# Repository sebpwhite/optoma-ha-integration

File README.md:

# Optoma Projector

Home Assistant custom integration for controlling an Optoma projector over
RS-232. It is designed to work with local serial ports and ESPHome serial
proxies through Home Assistant's serial port selector.

## Repository Layout

- `custom_components/optoma_projector/` contains the HACS-installable Home
  Assistant integration.
- `esphome/ProjectorController.yaml` contains the ESPHome firmware that exposes
  the projector UART as an ESPHome serial proxy.

## Basic Use

1. Flash the ESPHome firmware from `esphome/ProjectorController.yaml`.
2. Install the `optoma_projector` integration in Home Assistant.
3. Add the integration from the Home Assistant UI and select the ESPHome serial
   proxy from the serial port dropdown.

The current integration implements power, input selection, useful projector
settings, status sensors, and a re-sync action for the GT1080HDR.
Power state is polled regularly so Home Assistant notices manual power-button
changes and automatic shutdowns.

For detailed integration logs, enable debug logging for
`custom_components.optoma_projector`.

## Entities

- Media player: power and input source selection.
- Sensors: projector status, lamp hours, and temperature.
- Switches: AV mute, freeze, 3D mode, and 3D sync invert.
- Selects: display mode, aspect ratio, brightness mode, and 3D format.
- Numbers: brightness, contrast, and vertical keystone.
- Button: re-sync.

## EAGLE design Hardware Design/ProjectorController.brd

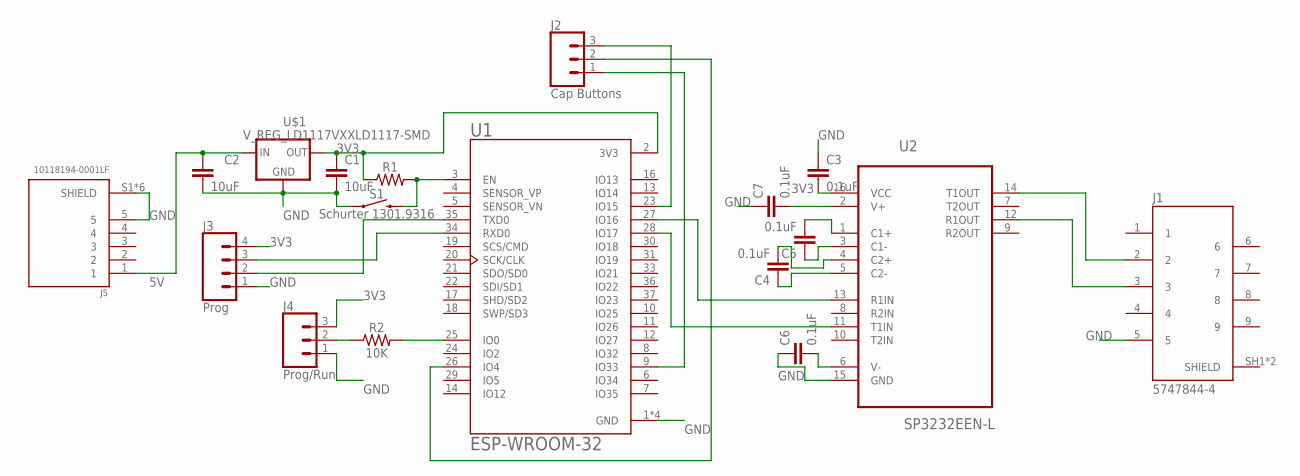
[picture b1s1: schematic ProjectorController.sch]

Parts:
C1, C2: 10uF; 1206
C3, C4, C5, C6, C7: 0.1uF; 1206
J1: 5747844-4; TE_5747844-4
J2: Cap Buttons; SCREWTERMINAL-3.5MM-3-NS
J3: Prog; 1X04
J4: Prog/Run; 1X03
J5: 10118194-0001LF; AMPHENOL_10118194-0001LF
R1: 1206
R2: 10K; 1206
S1: Schurter 1301.9316; TACTILE_SWITCH_SMD_6.2MM_TALL
U1: ESP-WROOM-32; MODULE_ESP-WROOM-32
U2: SP3232EEN-L; SOIC127P600X175-16N
U$1: V_REG_LD1117VXXLD1117-SMD; SOT223

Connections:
3V3: C1.1, C3.2, J3.4, J4.3, R1.1, U1.2 (3V3), U2.16 (VCC), U$1.2 (OUT)
5V: C2.1, J5.1, U$1.3 (IN)
GND: C1.2, C2.2, C3.1, C6.1, C7.1, J1.5, J3.1, J4.1, J5.5, J5.S1 (SHIELD), J5.S2 (SHIELD), J5.S3 (SHIELD), J5.S4 (SHIELD), J5.S5 (SHIELD), J5.S6 (SHIELD), S1.A2 (1), U1.1 (GND), U1.1.1 (GND), U1.15 (GND), U1.38 (GND), U2.15 (GND), U$1.1 (GND)
unnamed: J2.3, U1.23 (IO15)
unnamed: J2.1, U1.9 (IO33)
unnamed: J2.2, U1.26 (IO4)
unnamed: R1.2, S1.B2 (2), U1.3 (EN)
unnamed: R2.2, U1.25 (IO0)
unnamed: J4.2, R2.1
unnamed: J3.2, U1.35 (TXD0)
unnamed: J3.3, U1.34 (RXD0)
unnamed: U1.28 (IO17), U2.11 (T1IN)
unnamed: J1.2, U2.14 (T1OUT)
unnamed: J1.3, U2.12 (R1OUT)
unnamed: C5.2, U2.1 (C1+)
unnamed: U1.27 (IO16), U2.13 (R1IN)
unnamed: C5.1, U2.3 (C1-)
unnamed: C4.2, U2.4 (C2+)
unnamed: C4.1, U2.5 (C2-)
unnamed: C7.2, U2.2 (V+)
unnamed: C6.2, U2.6 (V-)

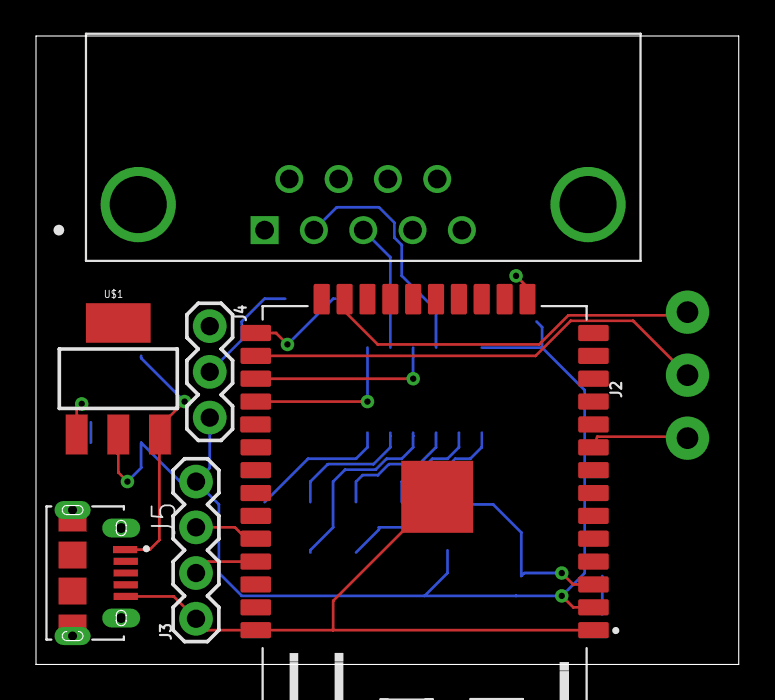
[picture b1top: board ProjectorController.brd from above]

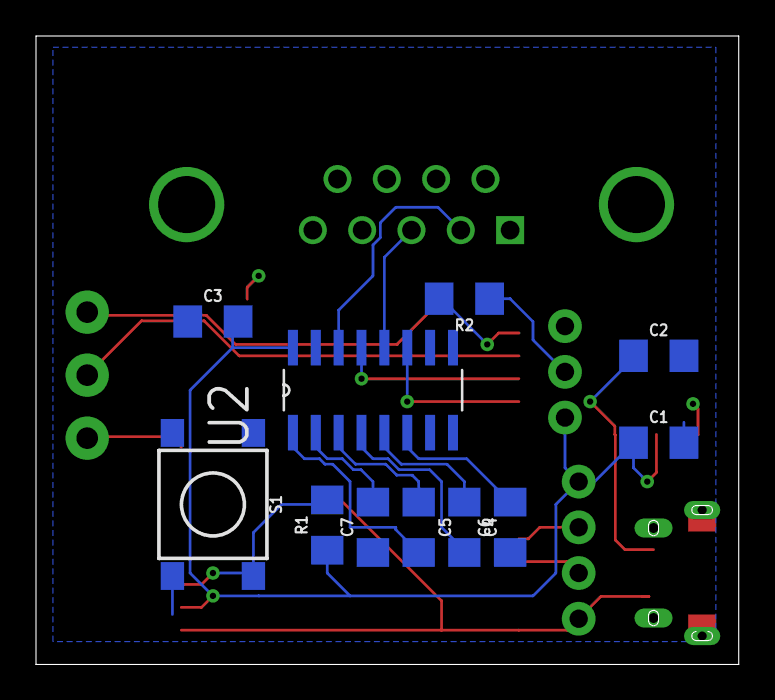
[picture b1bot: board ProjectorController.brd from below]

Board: 2 copper layers, 39.0 x 34.9 mm, 18 parts (11 on the bottom side), 21 nets.

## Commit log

2020-01-25 First cut of firmware with simple on/off commands working. PC-6
2020-01-25 Added touch sensor stuff and tied to to switches
2020-01-25 Revert "Added touch sensor stuff and tied to to switches"
    This reverts commit 2cf4c3fe7aaaa9ff7bf1352f440d9ed528192ab9.
2020-01-25 Revert "Revert "Added touch sensor stuff and tied to to switches""
    This reverts commit 99066c4c33003fed9244670f1164241629220ea0.
2020-01-25 First crack at custom component polling power state PC-10
2020-01-27 Custom Component Running Well
2020-01-28 Schematic started. PC-11
2020-01-29 USB port added and rough cut of schematic done. PC-11
2020-01-30 Progress on board layout PC-13
2020-01-31 Switched UART Pins PC-12
2020-02-01 Board Layout Complete PC-13
2020-02-02 Optimised Layout
2020-05-02 ED-33 Major board redesign to make smaller
2020-05-02 Revert "ED-33 Major board redesign to make smaller"
    This reverts commit ff5836e82a7b4c6ccf7f1796d2610aee96480eab.
2020-05-02 Revert "Revert "ED-33 Major board redesign to make smaller""
    This reverts commit 3ae201e74c16ce24ee355c7bdbcad0014f833ec8.
2020-05-09 PC-16 and other fixes
2020-05-09 First go at PC-18
2026-05-19 Complete rewrite to use esphome serial proxy and ha integration
2026-05-19 Fix Github handle
2026-05-19 Remove outdated secrets
2026-05-19 Simplify Serial config
2026-05-19 Add richer feature set with Codex
2026-05-30 Add regular state polling
2026-05-31 Fix polling bugs

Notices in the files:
parts and their libraries:
SparkFun-Capacitors: Licensing: Creative Commons ShareAlike 4.0 International - https://creativecommons.org/licenses/by-sa/4.0
